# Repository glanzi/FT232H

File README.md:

# FT232H Breakout

The FT232H breakout is a general purpose USB to GPIO, SPI and I2C board.

## License
The FT232H Breakout project is an open source project licensed under CERN Open Hardware Licence v1.2. Please see the included LICENSE file for details. If you do wish to distribute boards derived from this open source hardware project then you must also release the source files for the boards under CERN Open Hardware Licence v1.2. You are free to do this, but please improve upon the original design and provide a tangible benefit for users of the board.

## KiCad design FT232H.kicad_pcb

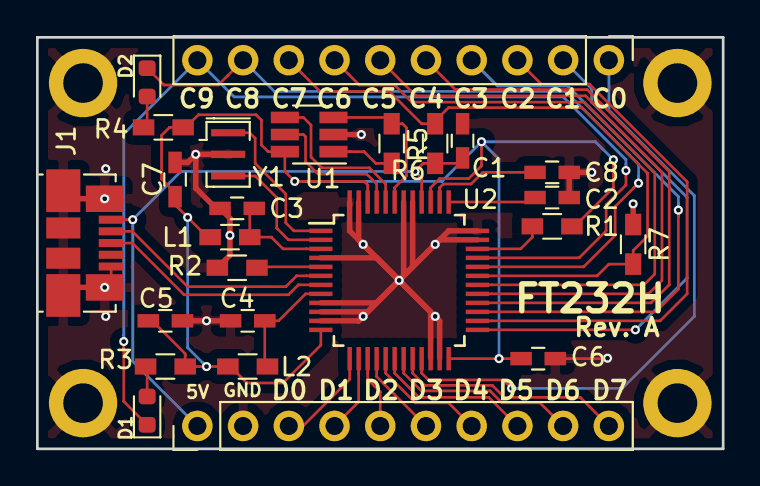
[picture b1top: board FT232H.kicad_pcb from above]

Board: 2 copper layers, 38.1 x 22.9 mm, 25 parts (0 on the bottom side), 37 nets.

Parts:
C1, C3, C4, C5: 10uF; C_0603_HandSoldering
C2, C6, C7, C8: 0.1uF; C_0603_HandSoldering
D1: Green; LED_0603_1608Metric
D2: Red; LED_0603_1608Metric
J1: USB_B_Micro; USB_Micro-B_Molex_47346-0001
J2, J3: Conn_01x10; PinHeader_1x10_P2.54mm_Vertical
L1, L2: 600; L_0603_HandSoldering
R1, R7: 12K; R_0603_HandSoldering
R2: 12K 1%; R_0603_HandSoldering
R3, R4: 1K; R_0603_HandSoldering
R5: 2.2K; R_0603_HandSoldering
R6: 4.7K; R_0603_HandSoldering
U1: 93LC56B; SOT-23-6_Handsoldering
U2: FT232H; LQFP-48_7x7mm_Pitch0.5mm
Y1: 12MHz; Resonator_SMD_muRata_CSTxExxV-3Pin_3.0x1.1mm

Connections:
+1V8: C8.1, U2.38
+3V3: C5.1, C6.1, C7.1, L1.2, L2.1, R1.2, R3.1, R4.1, U1.6, U2.12, U2.24, U2.39, U2.46
+5V: C1.1, J1.1, J2.1, R6.2, U2.40
GND: C1.2, C2.2, C3.2, C4.2, C5.2, C6.2, C7.2, C8.2, J1.5, J1.6, J2.2, R2.2, R7.1, U1.2, U2.4, U2.9, U2.10, U2.11, U2.22, U2.23, U2.35, U2.36, U2.41, U2.42, U2.47, U2.48, Y1.2
unnamed: C2.1, U2.37
unnamed: C3.1, L1.1, U2.3
unnamed: C4.1, L2.2, U2.8
unnamed: D1.1, J3.10, U2.33
unnamed: D1.2, R3.2
unnamed: D2.1, J3.9, U2.32
unnamed: D2.2, R4.2
unnamed: J1.2, U2.6
unnamed: J1.3, U2.7
unnamed: J2.3, U2.13
unnamed: J2.4, U2.14
unnamed: J2.5, U2.15
unnamed: J2.6, U2.16
unnamed: J2.7, U2.17
unnamed: J2.8, U2.18
unnamed: J2.9, U2.19
unnamed: J2.10, U2.20
unnamed: J3.1, U2.21
unnamed: J3.2, U2.25
unnamed: J3.3, U2.26
unnamed: J3.4, U2.27
unnamed: J3.5, U2.28
unnamed: J3.6, U2.29
unnamed: J3.7, U2.30
unnamed: J3.8, R6.1, R7.2, U2.31
unnamed: R1.1, U2.34
unnamed: R2.1, U2.5
unnamed: R5.1, U1.3, U2.43
unnamed: R5.2, U1.1
unnamed: U1.4, U2.44
unnamed: U1.5, U2.45
unnamed: U2.1, Y1.1
unnamed: U2.2, Y1.3

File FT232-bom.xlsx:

Quantity | Reference | Value | Footprint | Manufacturer | MPN | Digikey
4 | C1 C3 C4 C5 | 10uF | Capacitors_SMD:C_0603_HandSoldering
4 | C2 C6 C7 C8 | 0.1uF | Capacitors_SMD:C_0603_HandSoldering
1 | D1 | Green | LED_SMD:LED_0603_1608Metric
1 | D2 | Red | LED_SMD:LED_0603_1608Metric
1 | J1 | USB_B_Micro | Connector_USB:USB_Micro-B_Molex_47346-0001 |  |  | 609-4613-1-ND‎
2 | J2 J3 | Conn_01x10 | Connector_PinHeader_2.54mm:PinHeader_1x10_P2.54mm_Vertical
2 | L1 L2 | 600 | Inductors_SMD:L_0603_HandSoldering |  |  | ‎490-14039-1-ND‎
2 | R3 R4 | 1K | Resistors_SMD:R_0603_HandSoldering
1 | R5 | 2.2K | Resistors_SMD:R_0603_HandSoldering
1 | R6 | 4.7K | Resistors_SMD:R_0603_HandSoldering
2 | R1, R7 | 12K | Resistors_SMD:R_0603_HandSoldering
1 | R2 | 12K 1% | Resistors_SMD:R_0603_HandSoldering
1 | U1 | 93LC56B | TO_SOT_Packages_SMD:SOT-23-6_Handsoldering |  |  | 93LC56BT-I/OTCT-ND‎
1 | U2 | FT232H | Housings_QFP:LQFP-48_7x7mm_Pitch0.5mm |  |  | 768-1101-1-ND‎
1 | Y1 | 12MHz | Crystal:Resonator_SMD_muRata_CSTxExxV-3Pin_3.0x1.1mm |  |  | 490-17943-1-ND‎
 | Green items may be substituted with parts that have identical or better specifi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
 | Red items may not be substituted with different part numbers

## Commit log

2018-11-23 Add PCB layout
2018-11-24 Add BOM
2018-11-24 Rename files
